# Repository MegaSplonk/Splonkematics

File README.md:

# Splonkematics
Kicad Design files for the MegaSplonk hardware

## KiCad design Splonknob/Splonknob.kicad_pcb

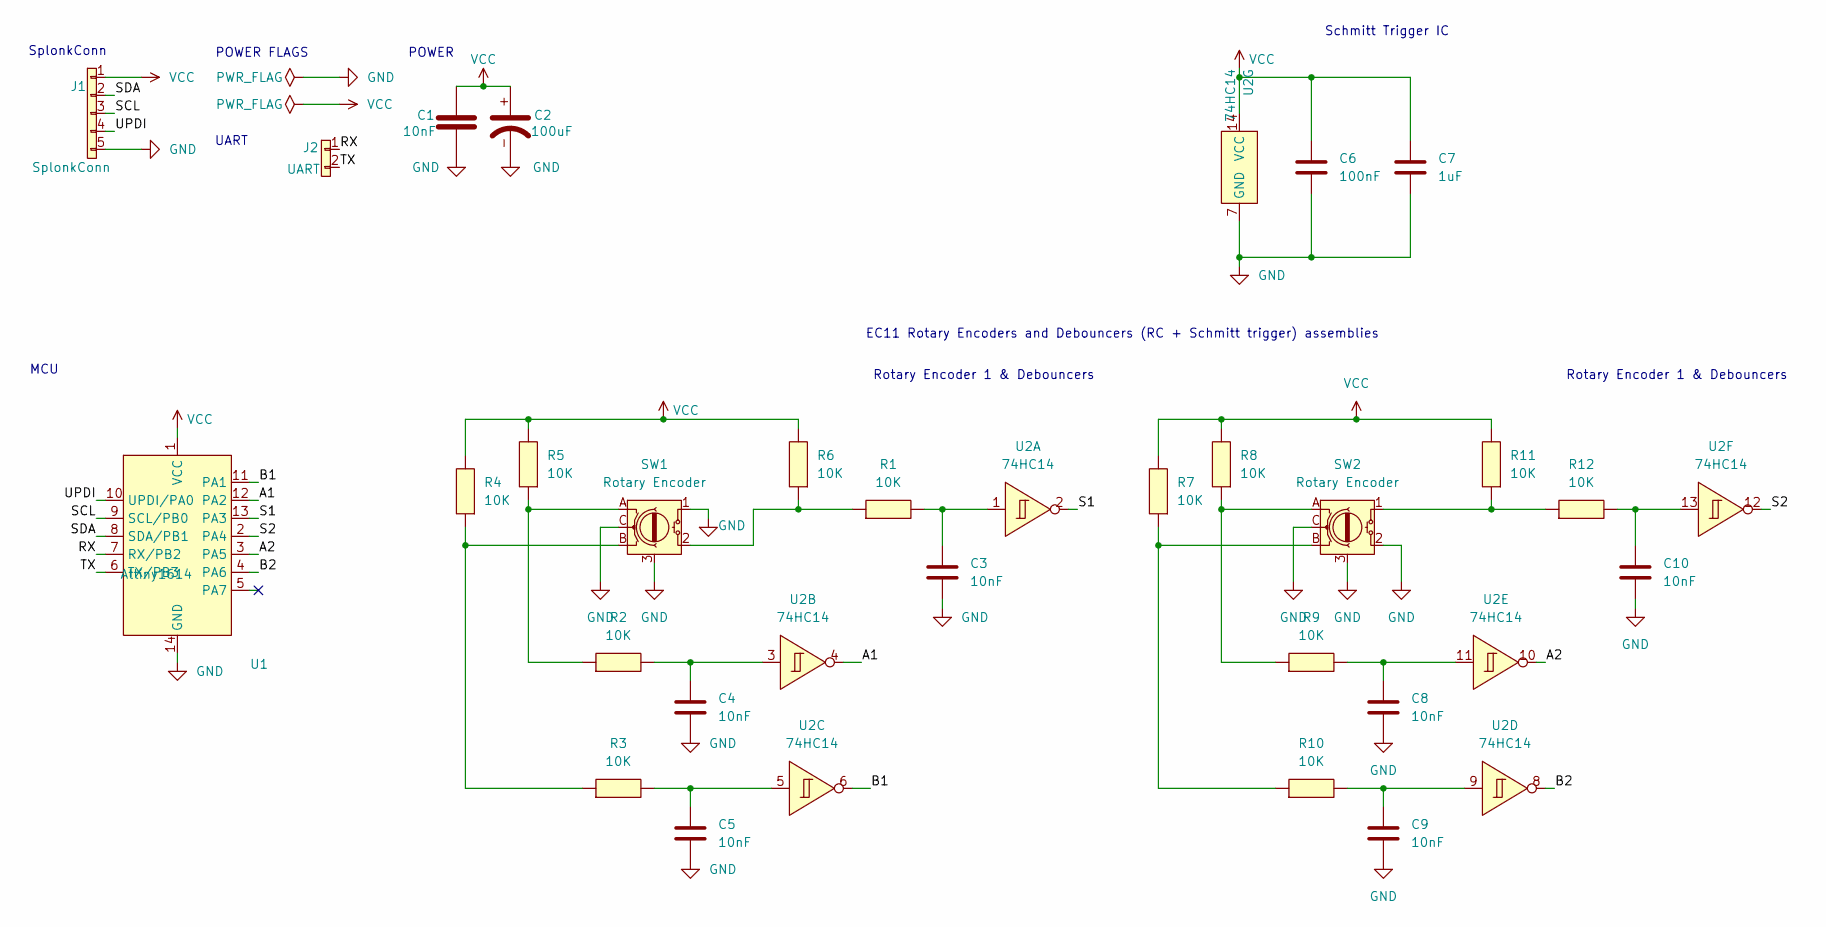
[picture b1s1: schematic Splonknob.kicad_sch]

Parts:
C1, C3, C4, C5, C8, C9, C10: 10nF; Capacitor_0603
C2: 100uF; ElectroliticCapacitor
C6: 100nF; Capacitor_0603
C7: 1uF; Capacitor_0603
J1: SplonkConn; MaixCon-5P
J2: UART; MaixCon-2P
R1, R2, R3, R4, R5, R6, R7, R8, R9, R10, R11, R12: 10K; Resistor_0603
SW1, SW2: Rotary Encoder; EC11E
U1: Attiny1614; SOIC-14
U2: 74HC14; SOIC-14

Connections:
/A1: U1.12 (PA2), U2.4
/A2: U1.3 (PA5), U2.10
/B1: U1.11 (PA1), U2.6
/B2: U1.4 (PA6), U2.8
/RX: J2.1, U1.7 (RX/PB2)
/S1: U1.13 (PA3), U2.2
/S2: U1.2 (PA4), U2.12
/SCL: J1.3, U1.9 (SCL/PB0)
/SDA: J1.2, U1.8 (SDA/PB1)
/TX: J2.2, U1.6 (TX/PB3)
/UPDI: J1.4, U1.10 (UPDI/PA0)
unnamed: C3.1, R1.2, U2.1
unnamed: C4.1, R2.2, U2.3
unnamed: C5.1, R3.2, U2.5
unnamed: C8.1, R9.2, U2.11
unnamed: C9.1, R10.2, U2.9
unnamed: C10.1, R12.2, U2.13
unnamed: R2.1, R5.1, SW1.A
unnamed: R3.1, R4.1, SW1.B
unnamed: R8.1, R9.1, SW2.A
unnamed: R7.1, R10.1, SW2.B
unnamed: R1.1, R6.1, SW1.2 (Switch^{2})
unnamed: R11.1, R12.1, SW2.1 (Switch^{1})

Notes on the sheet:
POWER FLAGS
SplonkConn
EC11 Rotary Encoders and Debouncers (RC + Schmitt trigger) assemblies
UART
MCU
Rotary Encoder 1 & Debouncers
POWER
Schmitt Trigger IC

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
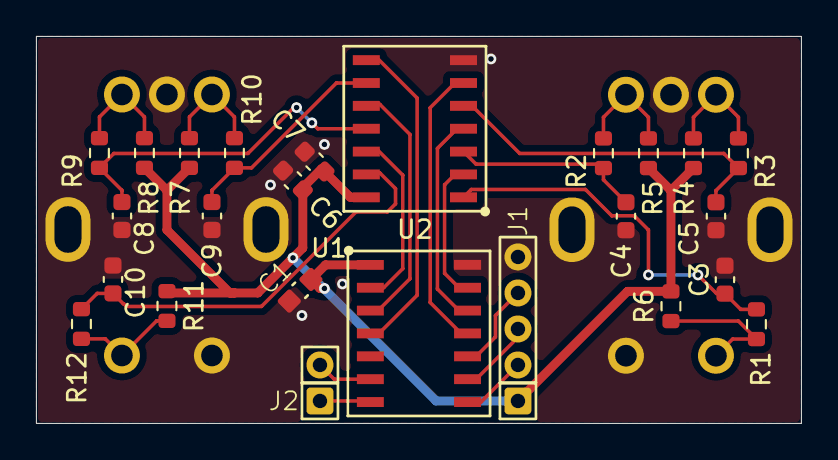
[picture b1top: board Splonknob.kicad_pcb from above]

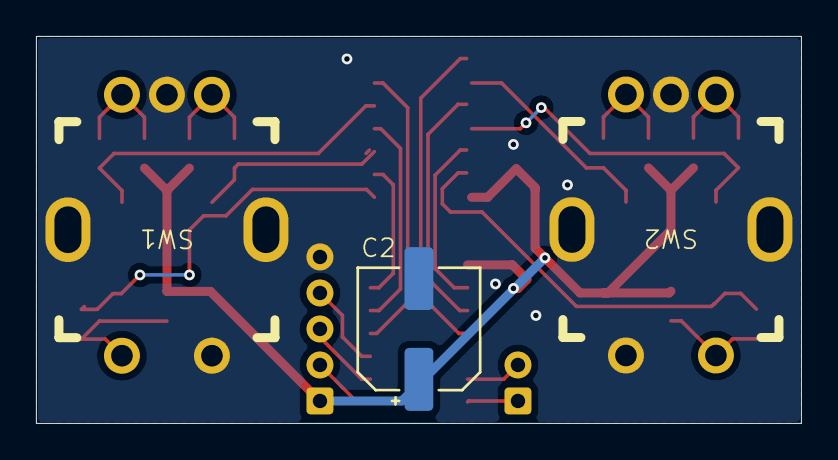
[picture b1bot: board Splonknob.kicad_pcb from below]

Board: 2 copper layers, 42.5 x 21.5 mm, 28 parts (3 on the bottom side), 25 nets.

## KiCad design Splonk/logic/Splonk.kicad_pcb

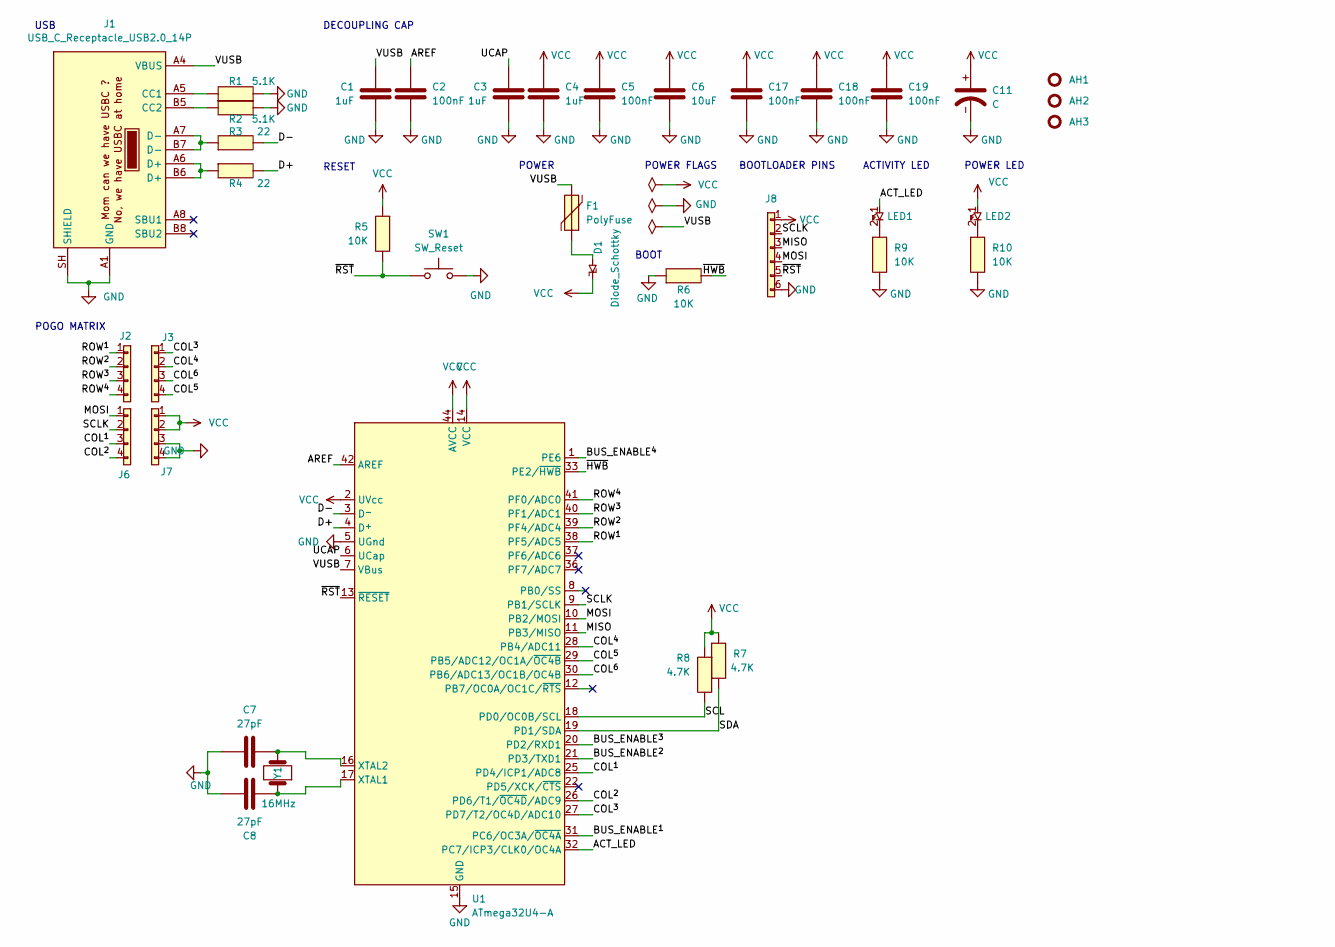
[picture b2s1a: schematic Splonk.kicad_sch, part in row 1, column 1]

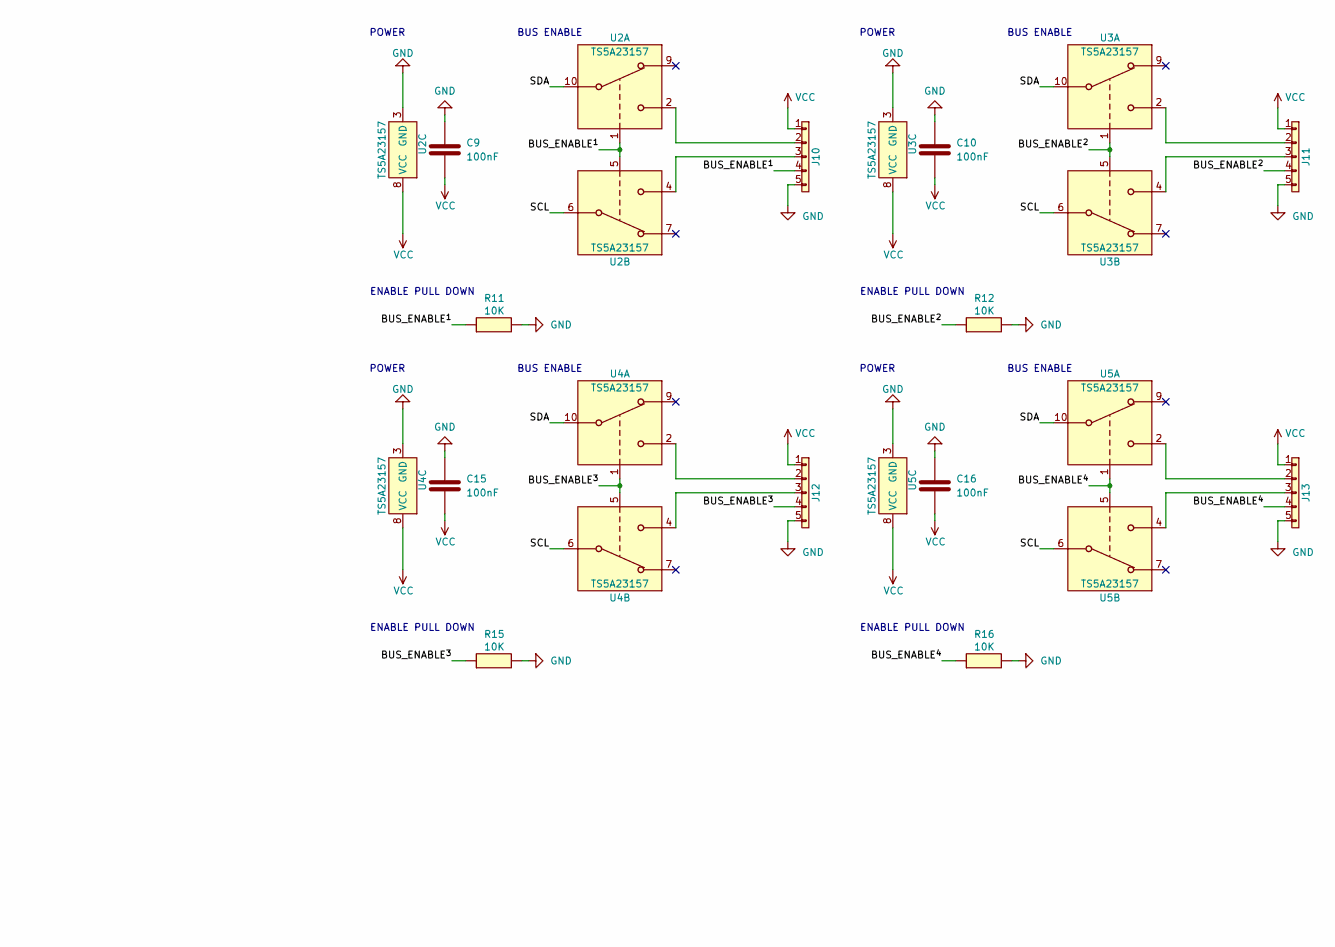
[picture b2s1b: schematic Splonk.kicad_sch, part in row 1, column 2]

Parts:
AH1, AH2, AH3: Alignment_Hole
C1, C3, C4: 1uF; Capacitor_0603
C2, C5, C9, C10, C15, C16, C17, C18, C19: 100nF; Capacitor_0603
C6: 10uF; Capacitor_0603
C7, C8: 27pF; Capacitor_0603
C11: C; ElectroliticCapacitor
D1: Diode_Schottky; Schottky
F1: PolyFuse; Fuse_1206
J1: USB_C_Receptacle_USB2.0_14P; USB-C
J2, J3, J6, J7: POGO; Pogo_4_pin
J8: Pin_header_6
J10, J11, J12, J13: SplonkConn; Pin_header_5
LED1, LED2: Diode_0603
R1, R2: 5.1K; Resistor_0603
R3, R4: 22; Resistor_0603
R5, R6, R9, R10, R11, R12, R15, R16: 10K; Resistor_0603
R7, R8: 4.7K; Resistor_0603
SW1: SW_Reset; SMD_Button
U1: ATmega32U4-A; TQFP-44_10x10_Pitch0.8mm
U2, U3, U4, U5: TS5A23157; MSOP-10
Y1: 16MHz; Quatz_16Mhz

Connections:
/ACT_LED: LED1.1, U1.32 (PC7/ICP3/CLK0/OC4A)
/AREF: C2.1, U1.42 (AREF)
/BUS_ENABLE^{1}: J10.4, R11.1, U1.31 (PC6/OC3A/~OC4A), U2.1, U2.5
/BUS_ENABLE^{2}: J11.4, R12.1, U1.21 (PD3/TXD1), U3.1, U3.5
/BUS_ENABLE^{3}: J12.4, R15.1, U1.20 (PD2/RXD1), U4.1, U4.5
/BUS_ENABLE^{4}: J13.4, R16.1, U1.1 (PE6), U5.1, U5.5
/COL^{1}: J6.3, U1.25 (PD4/ICP1/ADC8)
/COL^{2}: J6.4, U1.26 (PD6/T1/~OC4D/ADC9)
/COL^{3}: J3.1, U1.27 (PD7/T2/OC4D/ADC10)
/COL^{4}: J3.2, U1.28 (PB4/ADC11)
/COL^{5}: J3.4, U1.29 (PB5/ADC12/OC1A/~OC4B)
/COL^{6}: J3.3, U1.30 (PB6/ADC13/OC1B/OC4B)
/D+: R4.2, U1.4 (D^{+})
/D-: R3.2, U1.3 (D^{-})
/MISO: J8.3, U1.11 (PB3/MISO)
/MOSI: J6.1, J8.4, U1.10 (PB2/MOSI)
/ROW^{1}: J2.1, U1.38 (PF5/ADC5)
/ROW^{2}: J2.2, U1.39 (PF4/ADC4)
/ROW^{3}: J2.3, U1.40 (PF1/ADC1)
/ROW^{4}: J2.4, U1.41 (PF0/ADC0)
/SCL: R8.2, U1.18 (PD0/OC0B/SCL), U2.6, U3.6, U4.6, U5.6
/SCLK: J6.2, J8.2, U1.9 (PB1/SCLK)
/SDA: R7.2, U1.19 (PD1/SDA), U2.10, U3.10, U4.10, U5.10
/UCAP: C3.1, U1.6 (UCap)
/VUSB: C1.1, F1.1, J1.A4 (VBUS), J1.B4 (VBUS), U1.7 (VBus)
/~HWB: R6.2, U1.33 (PE2/~HWB)
/~RST: J8.5, R5.2, SW1.1, U1.13 (~RESET)
GND: C1.2, C2.2, C3.2, C4.2, C5.2, C6.2, C7.1, C8.2, C9.1, C10.1, C11.-, C15.1, C16.1, C17.2, C18.2, C19.2, J1.A1 (GND), J1.B1 (GND), J1.SH (SHIELD), J7.3, J7.4, J8.6, J10.5, J11.5, J12.5, J13.5, R1.2, R2.2, R6.1, R9.2, R10.2, R11.2, R12.2, R15.2, R16.2, SW1.2, U1.5 (UGnd), U1.15 (GND), U1.23 (GND), U1.35 (GND), U1.43 (GND), U2.3 (GND), U3.3 (GND), U4.3 (GND), U5.3 (GND)
unnamed: D1.2, F1.2
unnamed: J1.A5 (CC1), R1.1
unnamed: J1.B5 (CC2), R2.1
unnamed: J1.A6 (D+), J1.B6 (D+), R4.1
unnamed: J1.A7 (D-), J1.B7 (D-), R3.1
unnamed: J10.2, U2.2
unnamed: J10.3, U2.4
unnamed: J11.2, U3.2
unnamed: J11.3, U3.4
unnamed: J12.2, U4.2
unnamed: J12.3, U4.4
unnamed: J13.2, U5.2
unnamed: J13.3, U5.4
unnamed: LED1.2, R9.1
unnamed: LED2.2, R10.1
unnamed: C8.1, U1.17 (XTAL1), Y1.1
unnamed: C7.2, U1.16 (XTAL2), Y1.2
VCC: C4.1, C5.1, C6.1, C9.2, C10.2, C11.+, C15.2, C16.2, C17.1, C18.1, C19.1, D1.1, J7.1, J7.2, J8.1, J10.1, J11.1, J12.1, J13.1, LED2.1, R5.1, R7.1, R8.1, U1.2 (UVcc), U1.14 (VCC), U1.24 (AVCC), U1.34 (VCC), U1.44 (AVCC), U2.8 (VCC), U3.8 (VCC), U4.8 (VCC), U5.8 (VCC)

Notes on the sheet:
ENABLE PULL DOWN
POWER
ACTIVITY LED
BUS ENABLE
POWER FLAGS
POGO MATRIX
USB
POWER LED
RESET
DECOUPLING CAP
BOOT
BOOTLOADER PINS

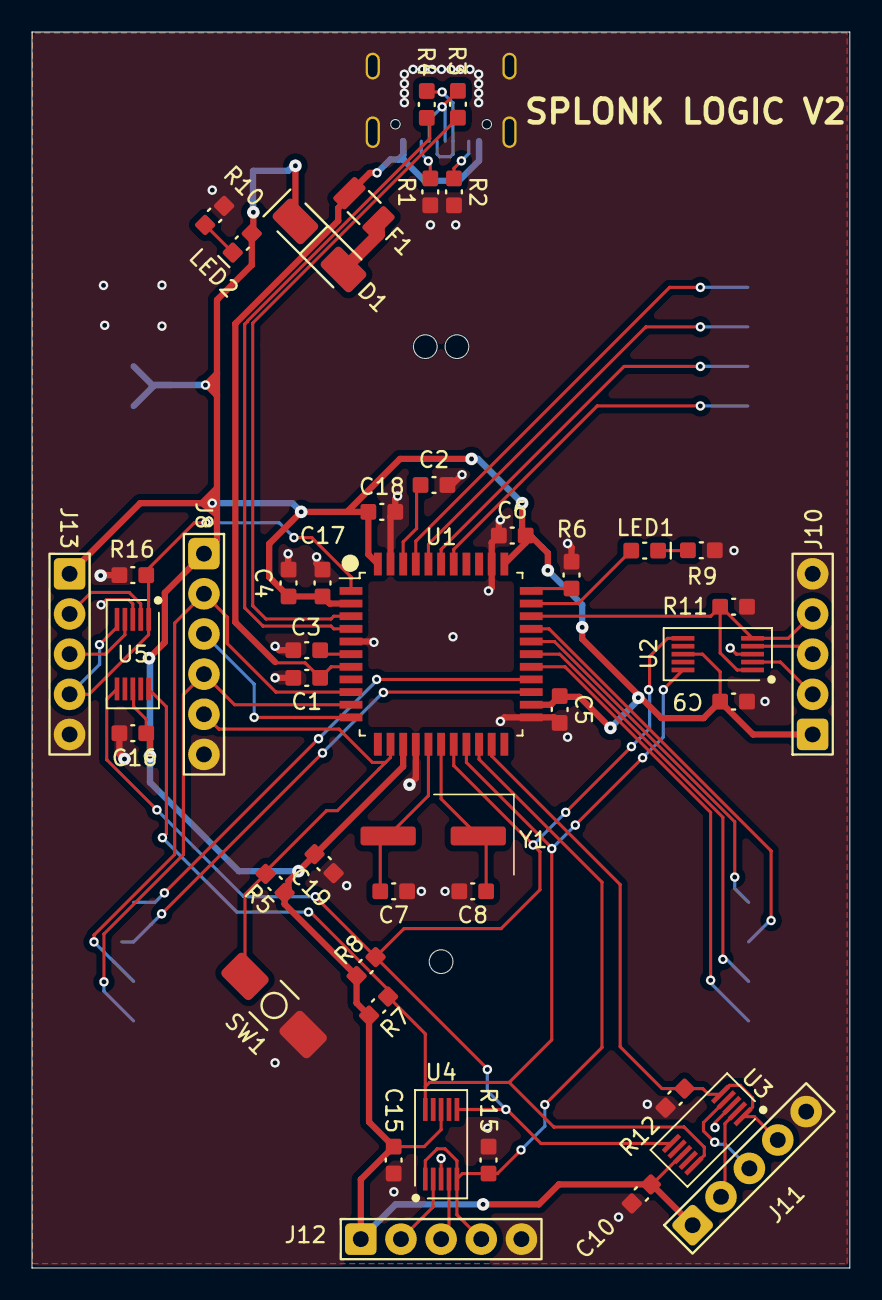
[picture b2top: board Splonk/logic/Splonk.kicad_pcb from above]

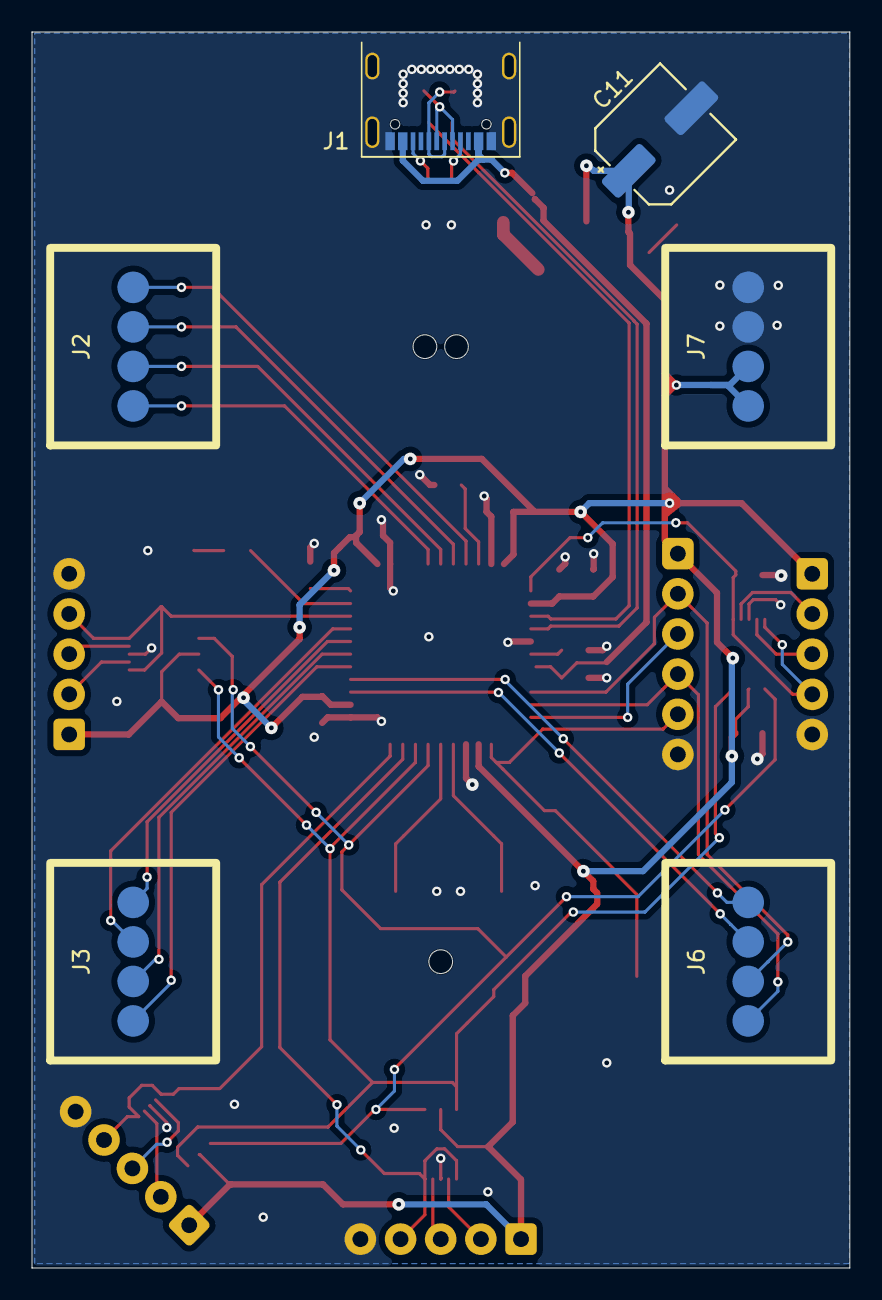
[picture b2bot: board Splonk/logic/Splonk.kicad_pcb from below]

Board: 2 copper layers, 51.7 x 78.2 mm, 54 parts (6 on the bottom side), 46 nets.

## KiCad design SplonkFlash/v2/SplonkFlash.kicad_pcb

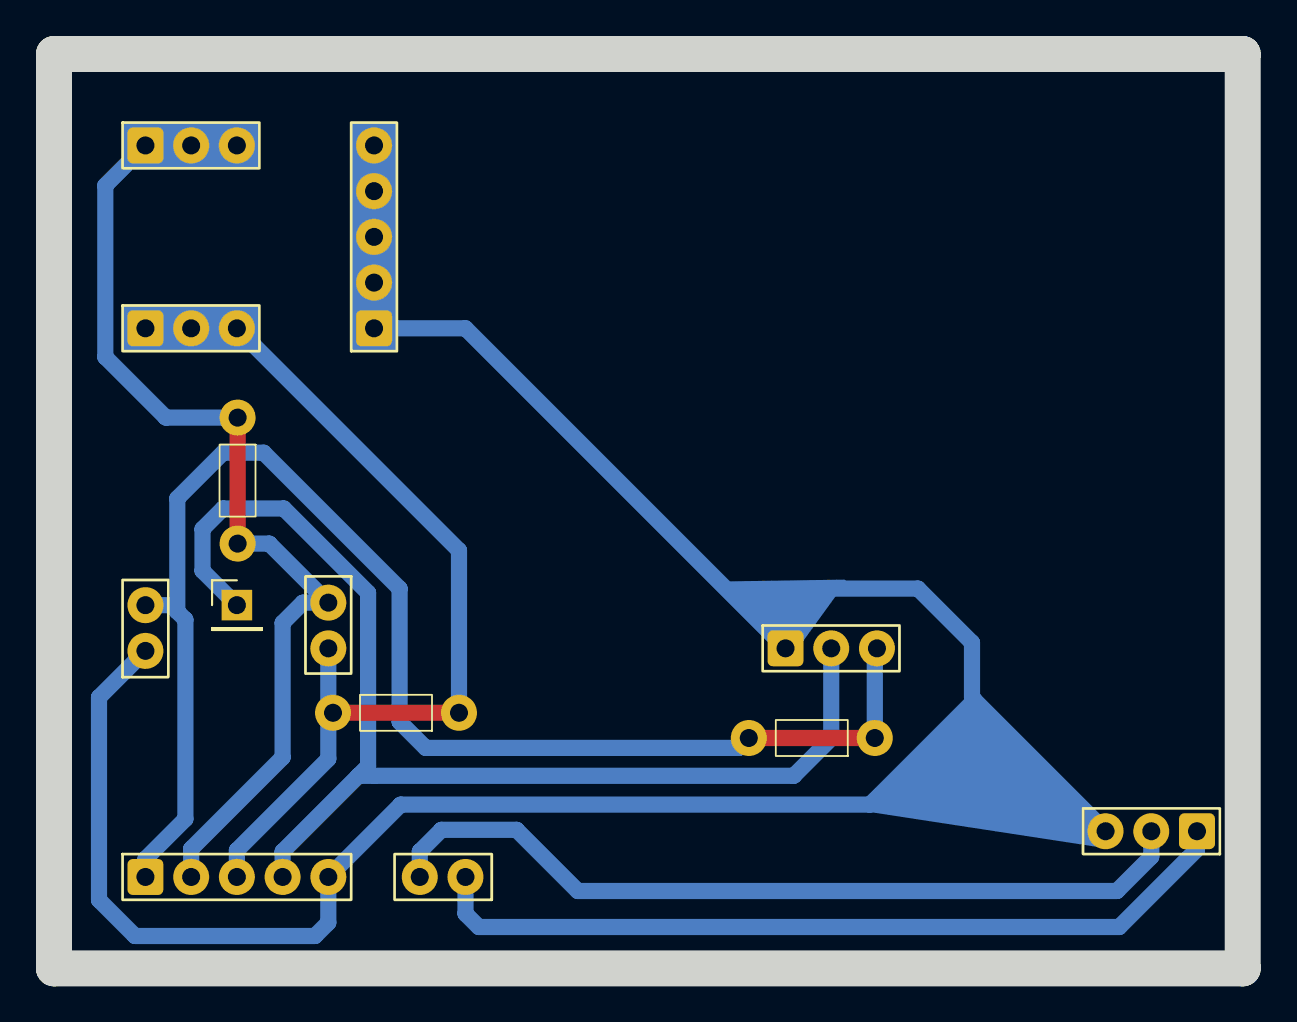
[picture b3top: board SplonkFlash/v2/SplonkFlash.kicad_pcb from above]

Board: 2 copper layers, 66.0 x 50.8 mm, 12 parts (0 on the bottom side), 7 nets.

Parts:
J1, J2, J4, J5: Pin_header_3
J3, J9: Pin_header_5
J6, J7, J8: Pin_header_2
J10: Conn_01x01_Pin; PinHeader_1x01_P2.54mm_Vertical
REF0, REF1: THT_Resistor

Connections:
/RX: J2.2, J8.2
/SCL: J5.1, J5.2, J5.3, J7.2, J9.3, REF0.1, REF0.2
/SDA: J4.1, J4.2, J4.3, J7.1, J9.2, REF1.1, REF1.2
/TX: J2.1, J8.1
/UDPI: J1.2, J9.4, J10.1 (Pin_1_1)
GND: J1.1, J2.3, J3.1, J3.2, J3.3, J3.4, J3.5, J6.1, J9.5
VCC: J1.3, J6.2, J9.1

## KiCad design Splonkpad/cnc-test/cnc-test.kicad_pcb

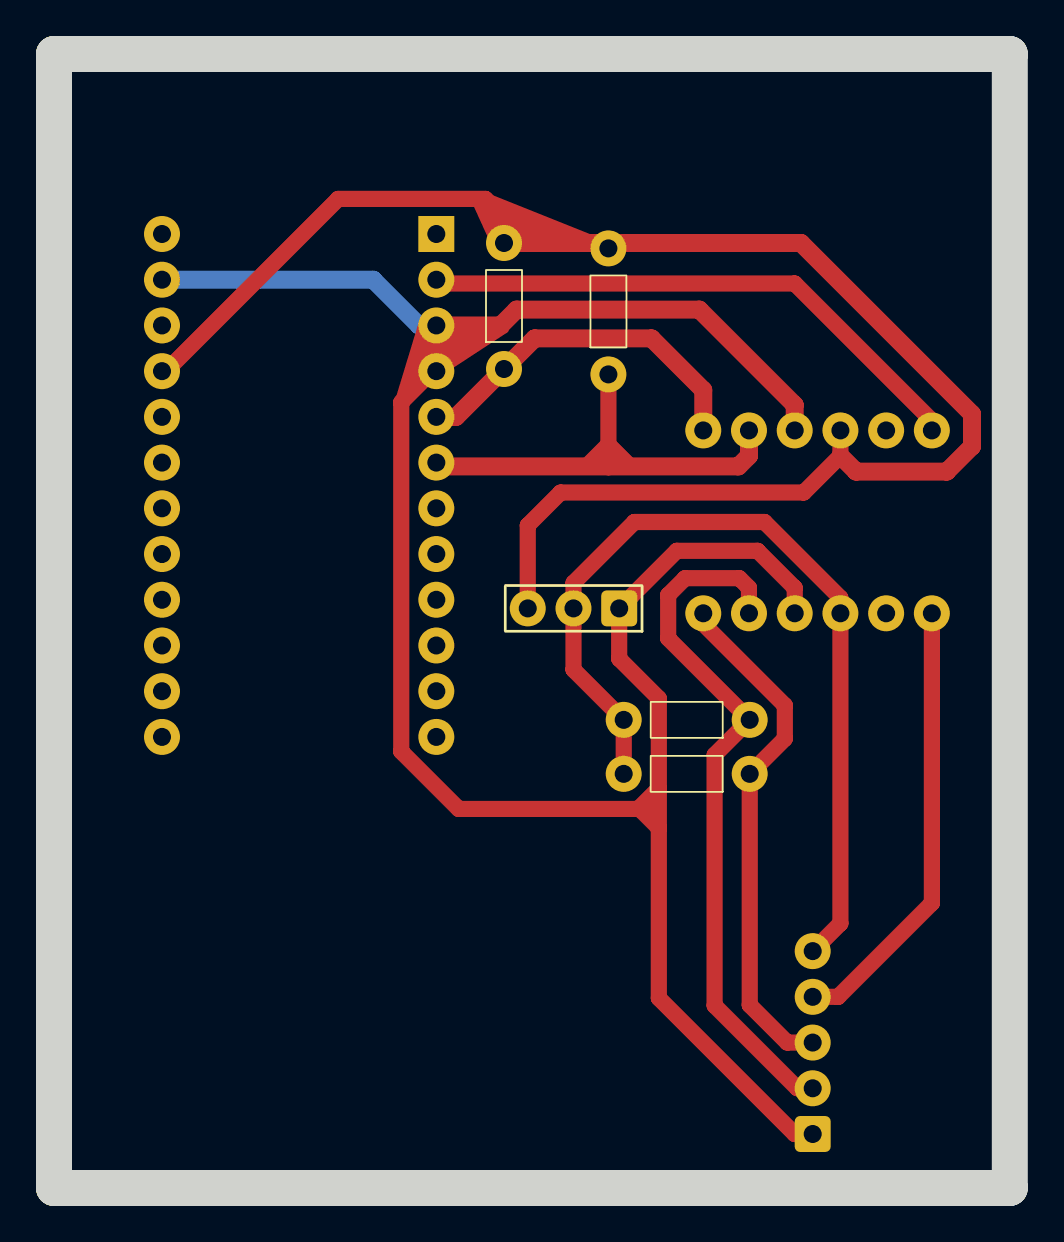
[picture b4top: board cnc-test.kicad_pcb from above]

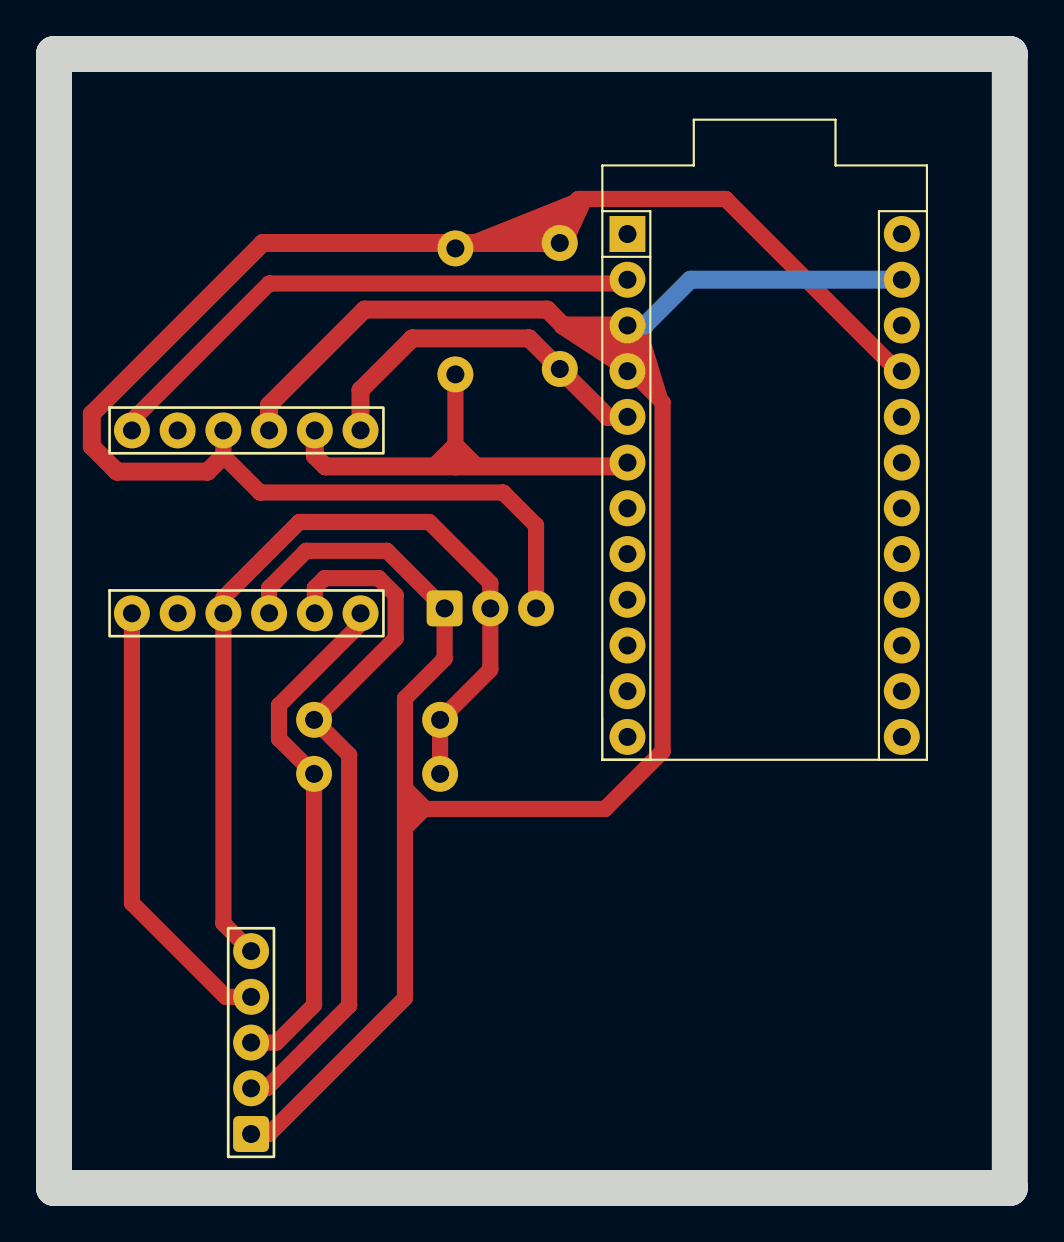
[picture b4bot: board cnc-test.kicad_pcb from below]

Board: 2 copper layers, 53.1 x 63.0 mm, 8 parts (3 on the bottom side), 9 nets.

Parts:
J1: Pin_header_3
J2: Pin_header_5
L1: NigelLevelShifter
M1: ProMicro
R1, R2, R3, R4: 10k; THT_Resistor

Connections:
3.3V: J1.2, J2.5, L1.9 (LV), R3.2, R4.2
/RDY: L1.1 (HV1), M1.2 (RX/D1)
/RDY^{3.3}: J2.4, L1.7 (LV1)
/SCL: L1.5 (HV3), M1.6 (SCL/D3), R1.1
/SCL^{3.3}: J2.2, L1.11 (LV3), R3.1
/SDA: L1.6 (HV4), M1.5 (SDA/D2), R2.1
/SDA^{3.3}: J2.3, L1.12 (LV4), R4.1
GND: J1.1, J2.1, L1.4 (GND), L1.10 (GND), M1.3 (GND), M1.4 (GND), M1.23 (GND)
VCC: J1.3, L1.3 (HV), M1.21 (VCC), R1.2, R2.2

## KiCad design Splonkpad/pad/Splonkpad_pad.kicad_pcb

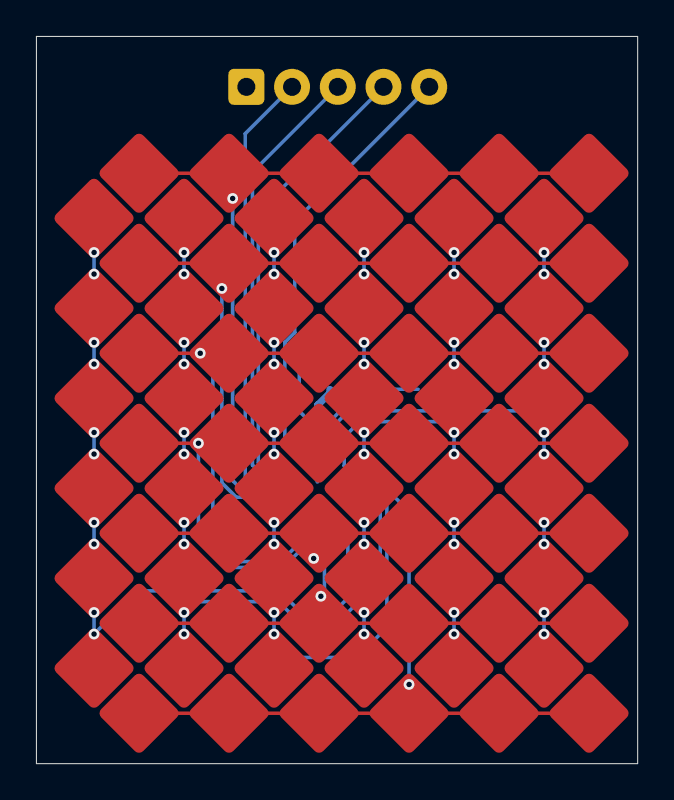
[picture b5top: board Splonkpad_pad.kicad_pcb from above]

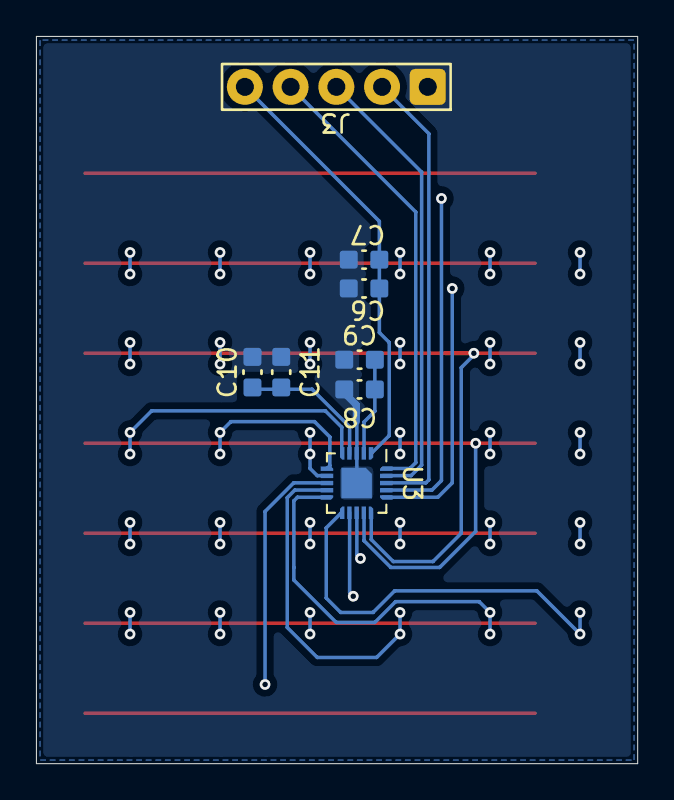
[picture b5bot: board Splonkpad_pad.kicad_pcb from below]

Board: 2 copper layers, 33.4 x 40.4 mm, 86 parts (8 on the bottom side), 20 nets.

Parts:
C6, C8, C10: 100pF; Capacitor_0603
C7: 4.7uF; Capacitor_0603
C9, C11: 2.2uF; Capacitor_0603
J3: Pad Conn; Pin_header_5
P2, P3, P4, P5, P6, P7, P8, P9, P10, P11, P12, P13, P14, P15, P16, P17, P18, P19, P20, P21, P22, P23, P24, P25, P26, P27, P28, P29, P30, P31, P32, P33, P34, P35, P36, P37, P38, P39, P40, P41, P42, P43, P44, P45, P46, P47, P48, P49, P50, P51, P52, P53, P54, P55, P56, P57, P58, P59, P60, P61, P62, P63, P64, P65, P66, P67, P68, P69, P70, P71, P72, P73, P74, P75, P76, P77, P78, P79: Pad
U3: IQS7211E; QFN-20_EP_3x3_Pitch0.4mm-

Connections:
3.3V: C6.1, C7.1, J3.5, U3.1 (VDD)
/RX0: P8.1, P20.1, P32.1, P44.1, P56.1, P68.1, U3.5 (RX0/TX0)
/RX1: P9.1, P21.1, P33.1, P45.1, P57.1, P69.1, U3.6 (RX1/TX1)
/RX2: P10.1, P22.1, P34.1, P46.1, P58.1, P70.1, U3.7 (RX2/TX2)
/RX4: P11.1, P23.1, P35.1, P47.1, P59.1, P71.1, U3.9 (RX4/TX4)
/RX5: P12.1, P24.1, P36.1, P48.1, P60.1, P72.1, U3.10 (RX5/TX5)
/RX6: P13.1, P25.1, P37.1, P49.1, P61.1, P73.1, U3.11 (RX6/TX6)
/SCL^{3.3P}: J3.2, U3.18 (SCL)
/SDA^{3.3P}: J3.3, U3.19 (SDA)
/TX3: P2.1, P3.1, P4.1, P5.1, P6.1, P7.1, U3.8 (RX3/TX3)
/TX7: P14.1, P15.1, P16.1, P17.1, P18.1, P19.1, U3.12 (RX7/TX7)
/TX8: P26.1, P27.1, P28.1, P29.1, P30.1, P31.1, U3.13 (TX8)
/TX9: P38.1, P39.1, P40.1, P41.1, P42.1, P43.1, U3.14 (TX9)
/TX10: P50.1, P51.1, P52.1, P53.1, P54.1, P55.1, U3.15 (TX10)
/TX11: P62.1, P63.1, P64.1, P65.1, P66.1, P67.1, U3.16 (TX11)
/TX12: P74.1, P75.1, P76.1, P77.1, P78.1, P79.1, U3.17 (TX12)
/VREGA: C10.1, C11.1, U3.4 (VREGA)
/VREGD: C8.1, C9.1, U3.2 (VREGD)
/~RST^{3.3P}: J3.4, U3.20 (RDY)
GND: C6.2, C7.2, C8.2, C9.2, C10.2, C11.2, J3.1, U3.3 (VSS), U3.21 (GND_TAB)

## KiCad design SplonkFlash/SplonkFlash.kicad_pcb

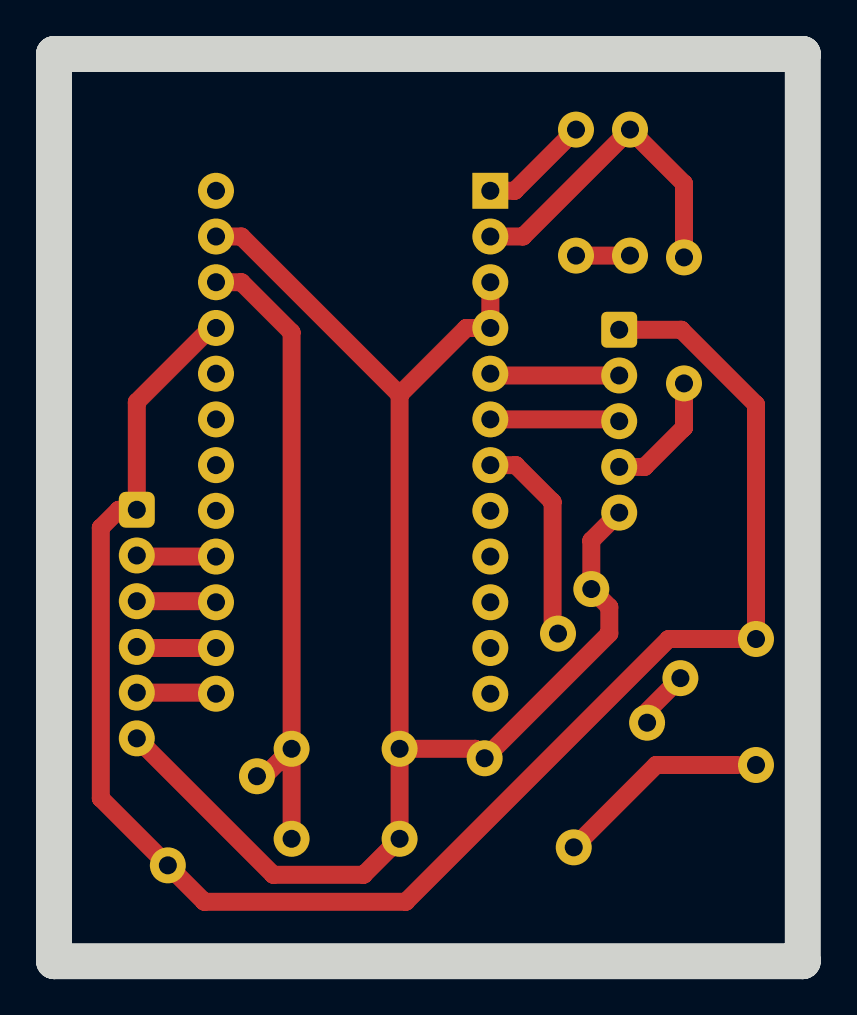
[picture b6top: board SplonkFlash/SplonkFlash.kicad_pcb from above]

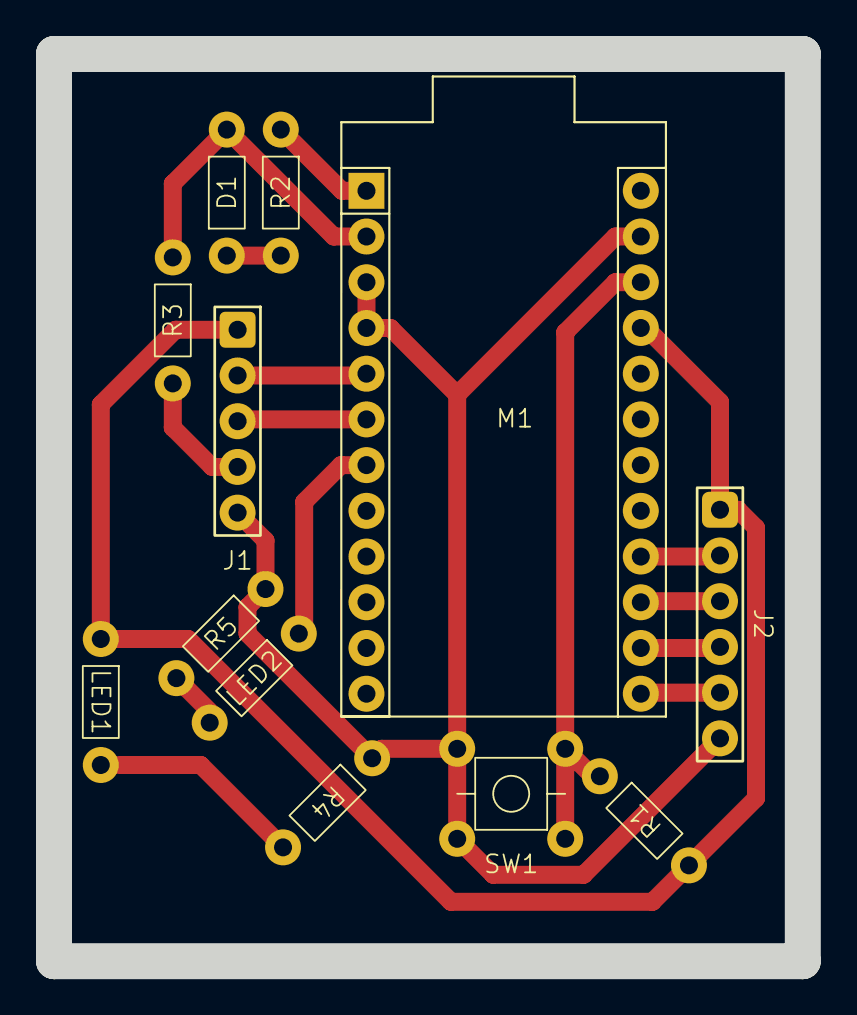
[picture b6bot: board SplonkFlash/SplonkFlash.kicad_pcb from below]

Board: 2 copper layers, 41.6 x 50.4 mm, 12 parts (12 on the bottom side), 16 nets.

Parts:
D1: THT_Resistor
J1: Pin_header_5
J2: Pin_header_6
LED1, LED2: THT_Resistor
M1: ProMicro
R1, R4, R5: 10k; THT_Resistor
R2: 1k; THT_Resistor
R3: 470; THT_Resistor
SW1: THT_Button

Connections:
/ACTIVE: LED2.1, M1.7 (PD4/D4)
/BOARD_RST: J2.5, M1.13 (PB6/D10)
/MISO: J2.3, M1.15 (MISO/PB3/D14)
/MOSI: J2.4, M1.14 (MOSI/PB2/D16)
/RX: D1.2, M1.2 (RX/D1), R3.1
/SCL: J1.3, M1.6 (SCL/D3)
/SCLK: J2.2, M1.16 (SCLK/PB1/D15)
/SDA: J1.2, M1.5 (SDA/D2)
/TX: M1.1 (TX/D0), R2.1
/UPDI: J1.4, R3.2
/~RST: M1.22 (~RST), R1.2, SW1.1
GND: J1.5, J2.6, M1.3 (GND), M1.4 (GND), M1.23 (GND), R4.1, R5.1, SW1.2
unnamed: D1.1, R2.2
unnamed: LED1.2, R4.2
unnamed: LED2.2, R5.2
VCC: J1.1, J2.1, LED1.1, M1.21 (VCC), R1.1
